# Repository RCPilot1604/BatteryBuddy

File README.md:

# BatteryBuddy
This is the repo for a project that aims to reduce reliance on single-use AA (NiMH/Alkaline) batteries by replacing them with modular, customizable Li-Ion battery packs for greater sustainability.

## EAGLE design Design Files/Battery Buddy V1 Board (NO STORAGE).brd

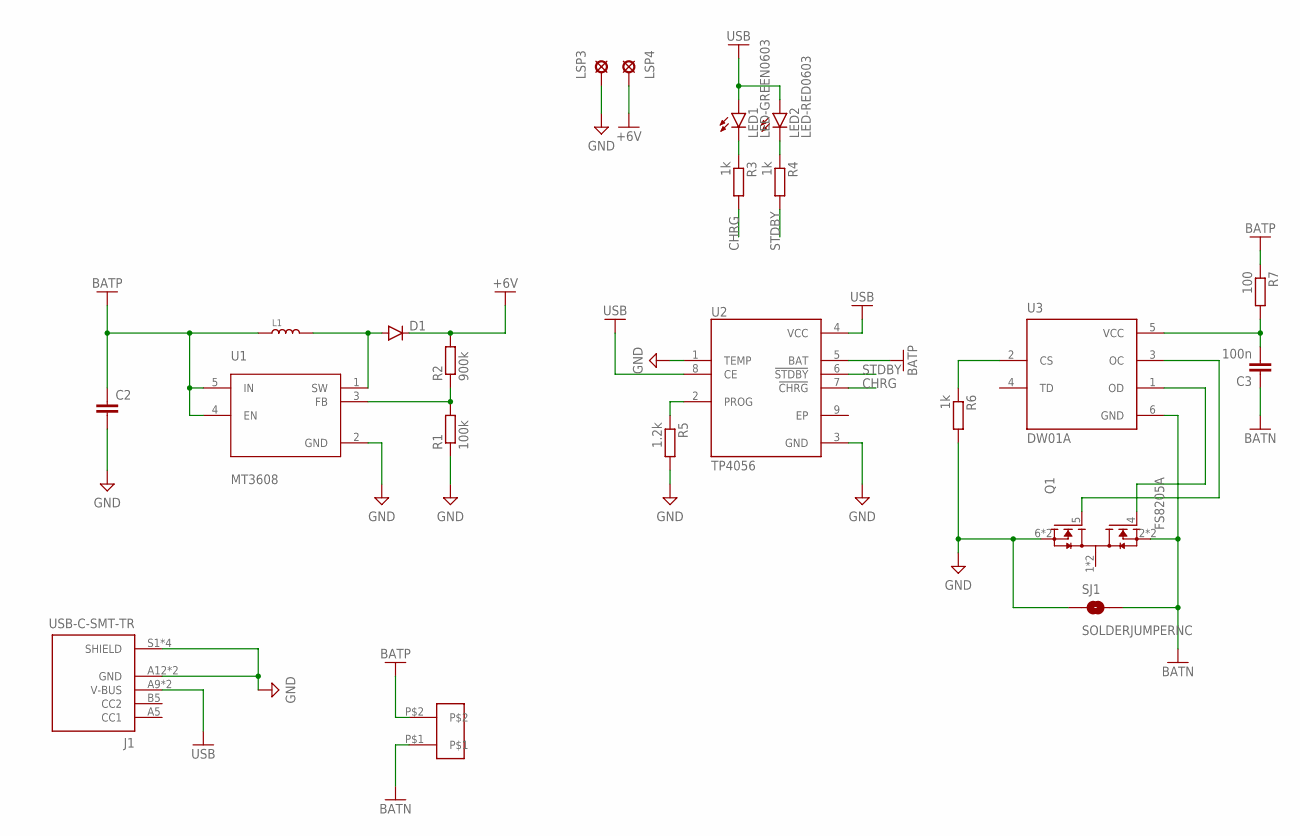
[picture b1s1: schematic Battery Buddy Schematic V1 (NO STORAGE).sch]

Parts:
C2: C-EUC0603; C0603
C3: 100n; C0603
D1: DIODEDO214AA; DO-214AA
J1: USB-C-SMT-TR; CUI_UJC-HP-3-SMT-TR
L1: INDUCTOR/FERRITE-BEAD0630; INDUCTOR_L0630
LED1: LED-GREEN0603; 0603-GREEN
LED2: LED-RED0603; 0603-RED
LSP3, LSP4: LSP10
Q1: FS8205A; SOP65P640X120-8N
R1: 100k; R0603
R2: 900k; R0603
R3, R4, R6: 1k; R0603
R5: 1.2k; R0603
R7: 100; R0603
SJ1: SOLDERJUMPERNC; SJ_2S
U1: MT3608; SOT95P280X145-6N
U2: TP4056; SOP127P600X175-9N
U3: DW01A; SOT95P280X145-6N
U$1: JST-ZH-2P

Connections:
+6V: D1.C, LSP4.MP, R2.2
BATN: C3.1, Q1.2 (S1), Q1.3 (S1), SJ1.2, U3.6 (GND), U$1.P$1
BATP: C2.1, L1.1, R7.1, U1.4 (EN), U1.5 (IN), U2.5 (BAT), U$1.P$2
CHRG: R3.2, U2.7 (!CHRG)
GND: C2.2, J1.A12 (GND), J1.B12 (GND), J1.S1 (SHIELD), J1.S2 (SHIELD), J1.S3 (SHIELD), J1.S4 (SHIELD), LSP3.MP, Q1.6 (S2), Q1.7 (S2), R1.1, R5.2, R6.2, SJ1.1, U1.2 (GND), U2.1 (TEMP), U2.3 (GND)
unnamed: LED1.C, R3.1
unnamed: LED2.C, R4.1
unnamed: R5.1, U2.2 (PROG)
unnamed: R6.1, U3.2 (CS)
unnamed: Q1.4 (G1), U3.1 (OD)
unnamed: Q1.5 (G2), U3.3 (OC)
unnamed: C3.2, R7.2, U3.5 (VCC)
unnamed: D1.A, L1.2, U1.1 (SW)
unnamed: R1.2, R2.1, U1.3 (FB)
STDBY: R4.2, U2.6 (!STDBY)
USB: J1.A9 (V-BUS), J1.B9 (V-BUS), LED1.A, LED2.A, U2.4 (VCC), U2.8 (CE)

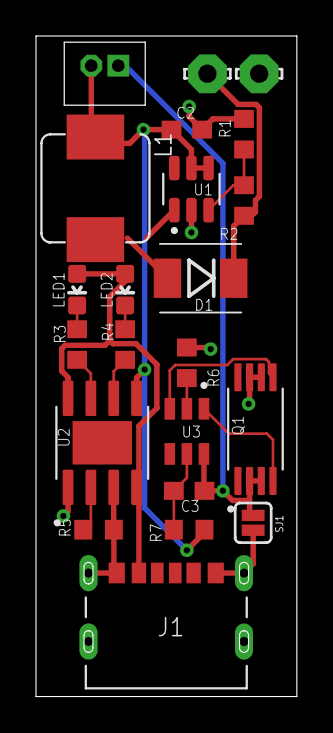
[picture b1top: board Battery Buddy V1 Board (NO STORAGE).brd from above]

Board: 2 copper layers, 14.5 x 36.7 mm, 22 parts (0 on the bottom side), 16 nets.

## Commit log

2025-05-22 Add V1 files

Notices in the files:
parts and their libraries:
SparkFun-Retired: Licensing: Creative Commons ShareAlike 4.0 International - https://creativecommons.org/licenses/by-sa/4.0
